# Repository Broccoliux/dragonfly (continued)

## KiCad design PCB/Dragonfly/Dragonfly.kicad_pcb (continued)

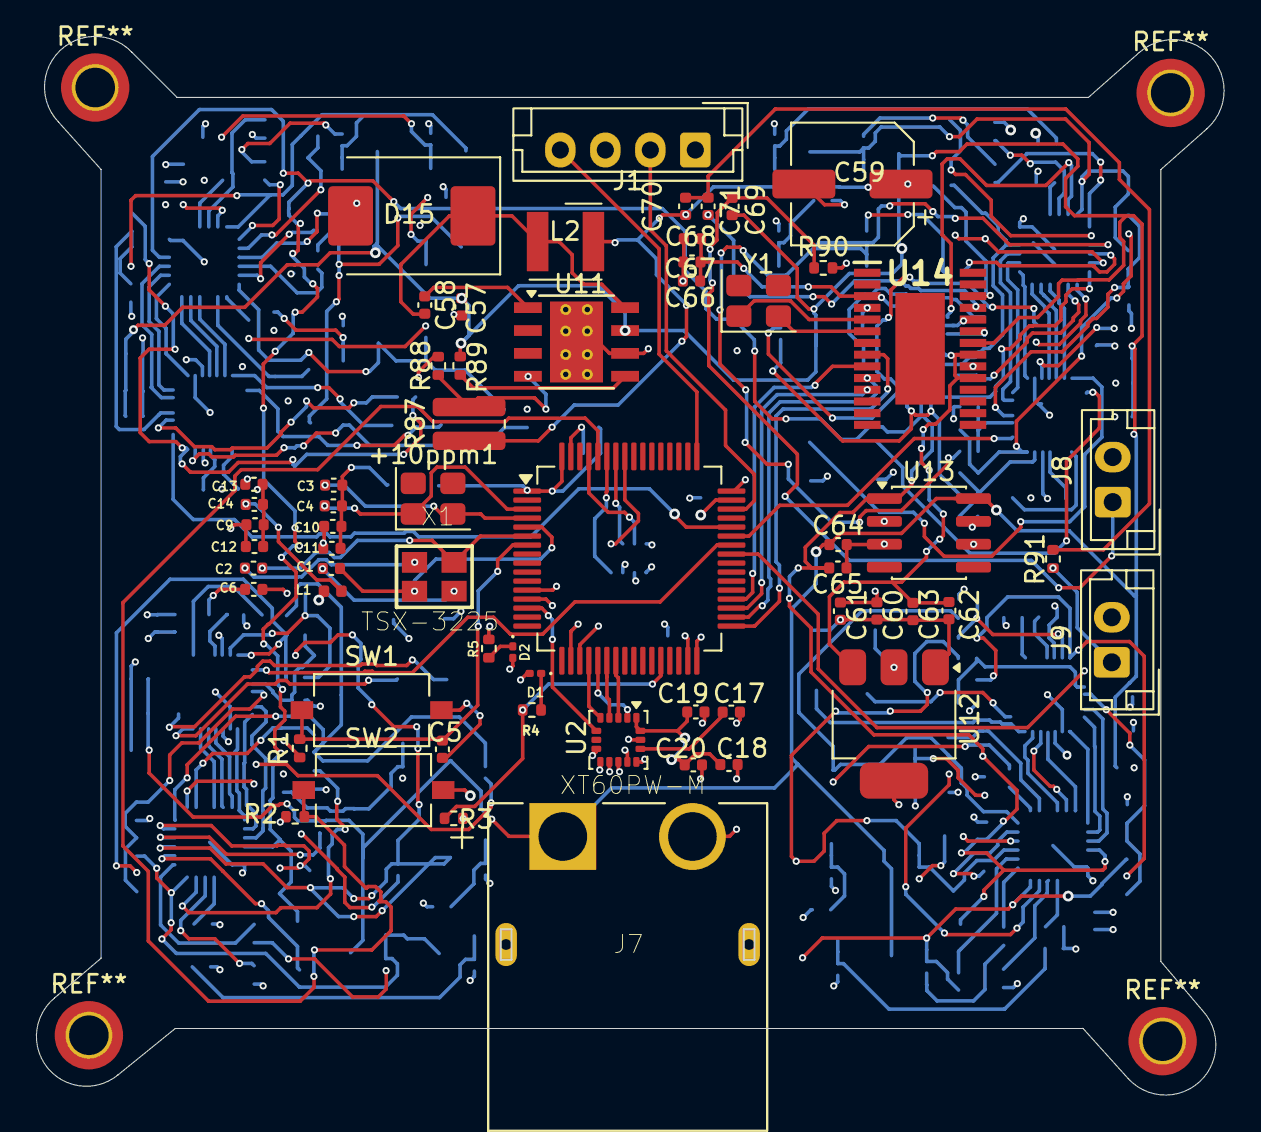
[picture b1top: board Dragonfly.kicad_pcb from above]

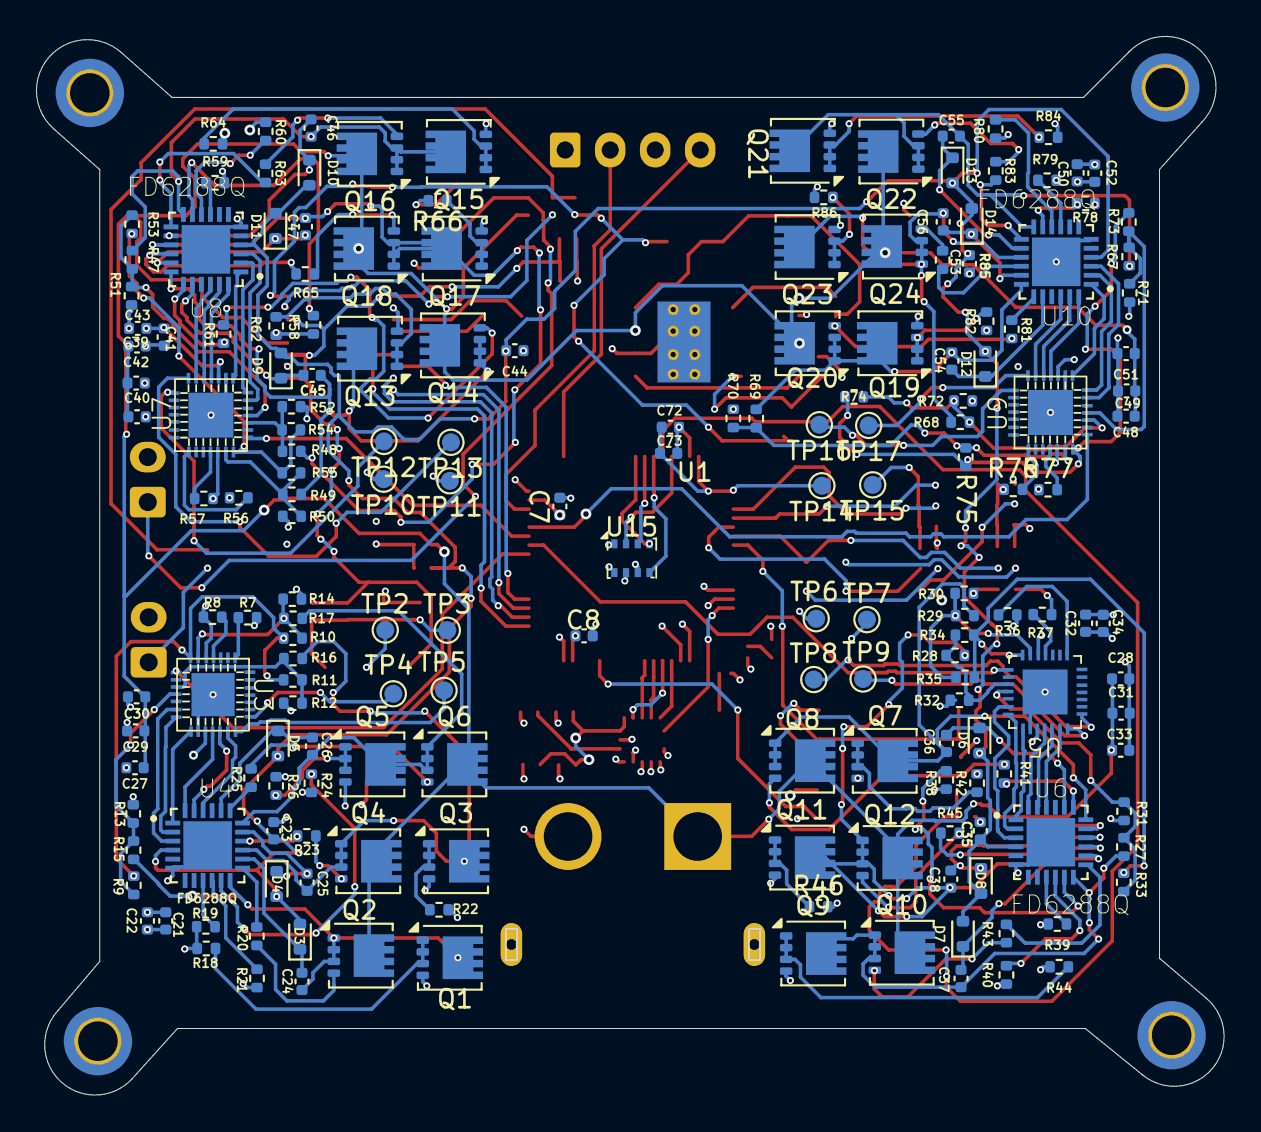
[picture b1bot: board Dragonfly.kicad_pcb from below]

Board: 4 copper layers, 66.0 x 58.8 mm, 242 parts (181 on the bottom side), 180 nets.

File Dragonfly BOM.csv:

"Reference","Qty","Value","DNP","Exclude from BOM","Exclude from Board","Footprint","Datasheet"
"+10ppm1","1","32.768 kHz","","","","Crystal:Crystal_SMD_3225-4Pin_3.2x2.5mm",""
"C1,C2","2","10pf","","","","Capacitor_SMD:C_0402_1005Metric",""
"C3,C4","2","12pf","","","","Capacitor_SMD:C_0402_1005Metric",""
"C5,C6,C9,C10,C11,C12,C17,C19,C21,C22,C23,C26,C32,C34,C35,C36,C41,C43,C44,C45,C50,C52,C53,C54,C64,C65,C66,C67,C68,C69","30","100nf","","","","Capacitor_SMD:C_0402_1005Metric",""
"C7,C8,C18","3","2.2uf","","","","Capacitor_SMD:C_0402_1005Metric",""
"C13","1","10nf","","","","Capacitor_SMD:C_0402_1005Metric",""
"C14,C61,C63,C72","4","1uf","","","","Capacitor_SMD:C_0402_1005Metric",""
"C20,C24,C25,C27,C28,C29,C30,C31,C33,C37,C38,C39,C40,C42,C46,C47,C48,C49,C51,C55,C56,C57,C60,C62","24","10uf","","","","Capacitor_SMD:C_0402_1005Metric",""
"C58","1","0.01uf","","","","Capacitor_SMD:C_0402_1005Metric",""
"C59","1","220uf","","","","Capacitor_SMD:CP_Elec_6.3x5.8",""
"C70,C71","2","47uf","","","","Capacitor_SMD:C_0402_1005Metric",""
"C73","1","0.1uf","","","","Capacitor_SMD:C_0402_1005Metric",""
"D1","1","LED BLUE","","","","LED_SMD:LED_0201_0603Metric",""
"D2","1","LED RED","","","","LED_SMD:LED_0201_0603Metric",""
"D3,D4,D5,D6,D7,D8,D9,D10,D11,D12,D13,D14","12","1N914WT","","","","Diode_SMD:D_SOD-523","http://www.mouser.com/ds/2/149/1N4148WT-461550.pdf"
"D15","1","40V, 3A Schottky","","","","Diode_SMD:D_SMC","http://www.jameco.com/Jameco/Products/ProdDS/1538777.pdf"
"J1","1","Conn_01x04_Pin","","","","Connector_JST:JST_EH_B4B-EH-A_1x04_P2.50mm_Vertical",""
"J7","1","XT60PW-M","","","","XT60PW-M:AMASS_XT60PW-M",""
"J8","1","CAM VIN","","","","Connector_JST:JST_EH_B2B-EH-A_1x02_P2.50mm_Vertical",""
"J9","1","VOUT","","","","Connector_JST:JST_EH_B2B-EH-A_1x02_P2.50mm_Vertical",""
"L1","1","1KΩ 100Mhz","","","","Inductor_SMD:L_0402_1005Metric",""
"L2","1","15uh","","","","Inductor_SMD_Wurth:L_Wurth_WE-LQSH-4020",""
"Q1,Q2,Q3,Q4,Q5,Q6,Q7,Q8,Q9,Q10,Q11,Q12,Q13,Q14,Q15,Q16,Q17,Q18,Q19,Q20,Q21,Q22,Q23,Q24","24","Q_NMOS_GDS","","","","Package_SON:Diodes_PowerDI3333-8",""
"R1","1","10k NC","","","","Resistor_SMD:R_0402_1005Metric",""
"R2,R3,R7,R8,R9,R10,R11,R15,R16,R17,R27,R28,R29,R33,R34,R35,R36,R37,R47,R48,R49,R53,R54,R55,R56,R57,R67,R68,R69,R73,R74,R75,R76,R77,R88","35","10k","","","","Resistor_SMD:R_0402_1005Metric",""
"R4,R5","2","5.1kΩ","","","","Resistor_SMD:R_0402_1005Metric",""
"R12,R13,R14,R30,R31,R32,R50,R51,R52,R70,R71,R72","12","1k","","","","Resistor_SMD:R_0402_1005Metric",""
"R18,R22,R26,R42,R44,R46,R62,R64,R66,R82,R84,R86","12","0R","","","","Resistor_SMD:R_0402_1005Metric",""
"R19,R20,R21,R23,R24,R25,R38,R39,R40,R41,R43,R45,R58,R59,R60,R61,R63,R65,R78,R79,R80,R81,R83,R85","24","20R","","","","Resistor_SMD:R_0402_1005Metric",""
"R87","1","30.9k","","","","Resistor_SMD:R_0815_2038Metric",""
"R89","1","100k","","","","Resistor_SMD:R_0402_1005Metric",""
"R90,R91","2","75R","","","","Resistor_SMD:R_0402_1005Metric",""
"SW1,SW2","2","SW_SPST","","","","Button_Switch_SMD:SW_Tactile_SPST_NO_Straight_CK_PTS636Sx25SMTRLFS",""
"TP2,TP6,TP10,TP14","4","VDD33","","","","TestPoint:TestPoint_Pad_D1.0mm",""
"TP3,TP7,TP11,TP15","4","GND","","","","TestPoint:TestPoint_Pad_D1.0mm",""
"TP4","1","SWCLK1","","","","TestPoint:TestPoint_Pad_D1.0mm",""
"TP5","1","SWDIO1","","","","TestPoint:TestPoint_Pad_D1.0mm",""
"TP8","1","SWCLK2","","","","TestPoint:TestPoint_Pad_D1.0mm",""
"TP9","1","SWDIO2","","","","TestPoint:TestPoint_Pad_D1.0mm",""
"TP12","1","SWCLK3","","","","TestPoint:TestPoint_Pad_D1.0mm",""
"TP13","1","SWDIO3","","","","TestPoint:TestPoint_Pad_D1.0mm",""
"TP16","1","SWCLK4","","","","TestPoint:TestPoint_Pad_D1.0mm",""
"TP17","1","SWDIO4","","","","TestPoint:TestPoint_Pad_D1.0mm",""
"U1","1","STM32F405RGTx","","","","Package_QFP:LQFP-64_10x10mm_P0.5mm","https://www.st.com/resource/en/datasheet/stm32f405rg.pdf"
"U2","1","ICM-20602","","","","Package_LGA:LGA-16_3x3mm_P0.5mm_LayoutBorder3x5y","http://www.invensense.com/wp-content/uploads/2016/10/DS-0001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"
"U3,U5,U7,U9","4","AT32F421G8U7","","","","Library:AT32F421G8U7",""
"U4,U6,U8,U10","4","FD6288Q","","","","FD6288Q:QFN50P400X400X90-25N",""
"U11","1","TPS5430DDA","","","","Package_SO:TI_SO-PowerPAD-8_ThermalVias","http://www.ti.com/lit/ds/symlink/tps5430.pdf"
"U12","1","AMS1117-3.3","","","","Package_TO_SOT_SMD:SOT-223-3_TabPin2","http://www.advanced-monolithic.com/pdf/ds1117.pdf"
"U13","1","L78L08_SO8","","","","Package_SO:SOIC-8_3.9x4.9mm_P1.27mm","http://www.st.com/content/ccc/resource/technical/document/da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"
"U14","1","AT7456E","","","","AT7456E:SOP65P640X120-29N",""
"U15","1","BMP280","","","","Package_LGA:Bosch_LGA-8_2x2.5mm_P0.65mm_ClockwisePinNumbering","https://ae-bst.resource.bosch.com/media/_tech/media/datashee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"
"X1","1","TSX-3225","","","","TSX-3225:TSX-3225",""
"Y1","1","27MHZ","","","","Crystal:Crystal_SMD_3225-4Pin_3.2x2.5mm",""
